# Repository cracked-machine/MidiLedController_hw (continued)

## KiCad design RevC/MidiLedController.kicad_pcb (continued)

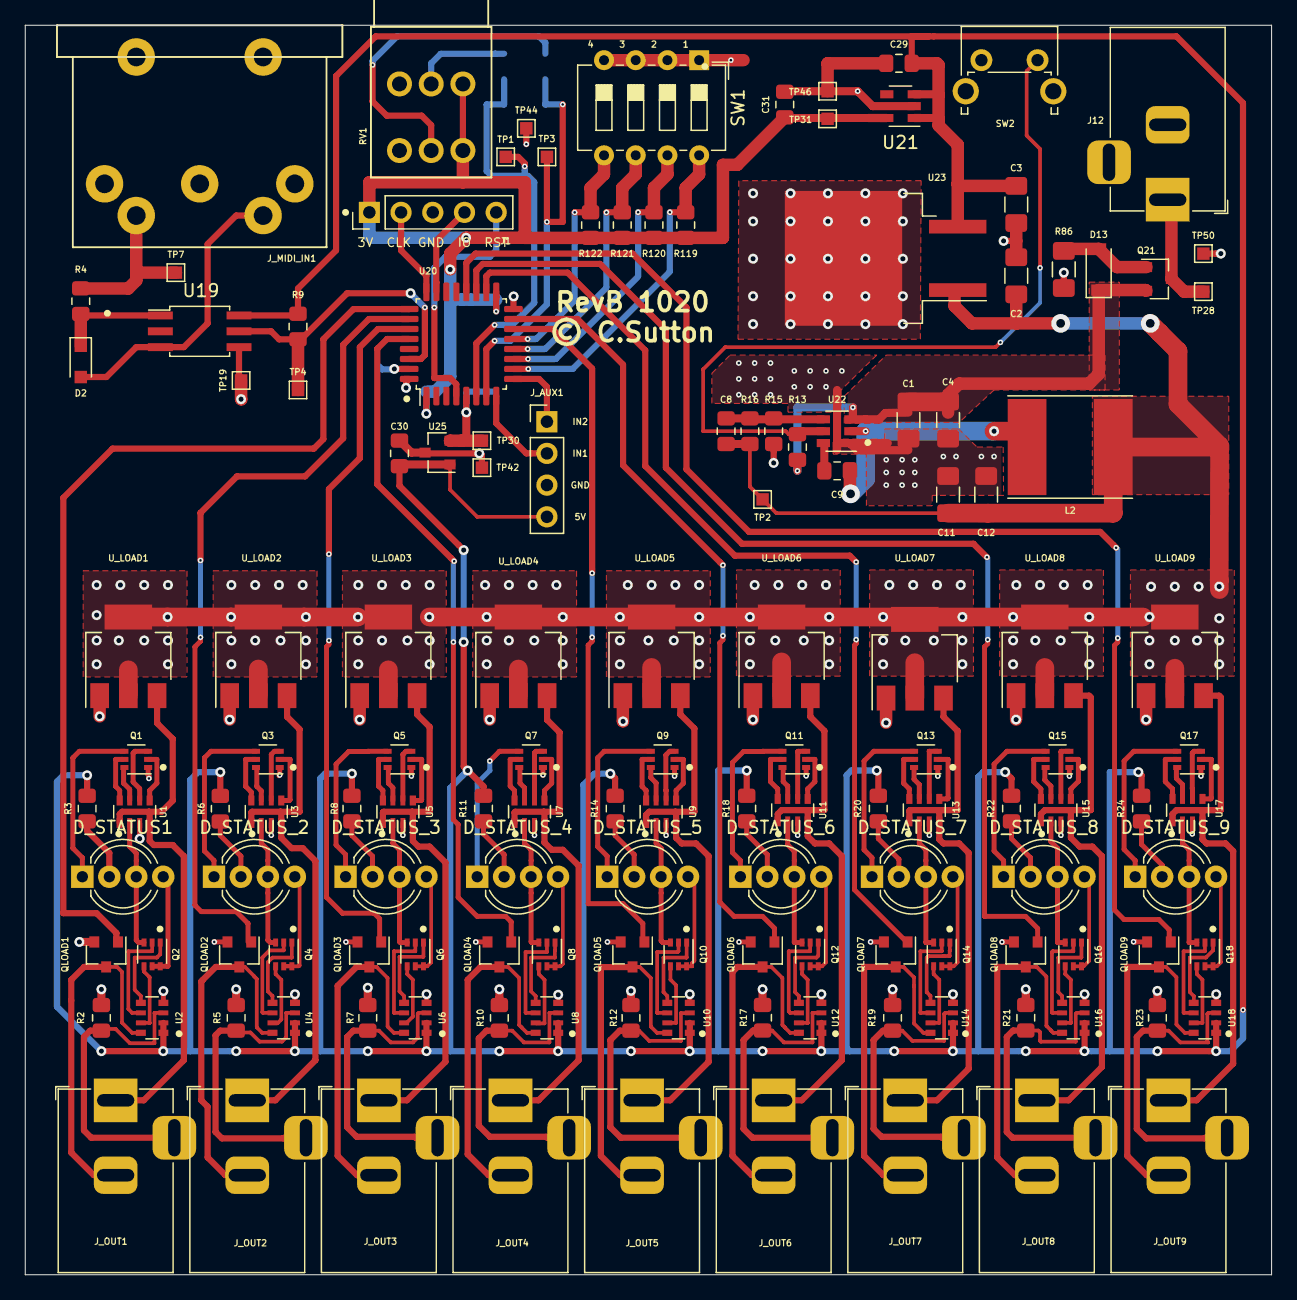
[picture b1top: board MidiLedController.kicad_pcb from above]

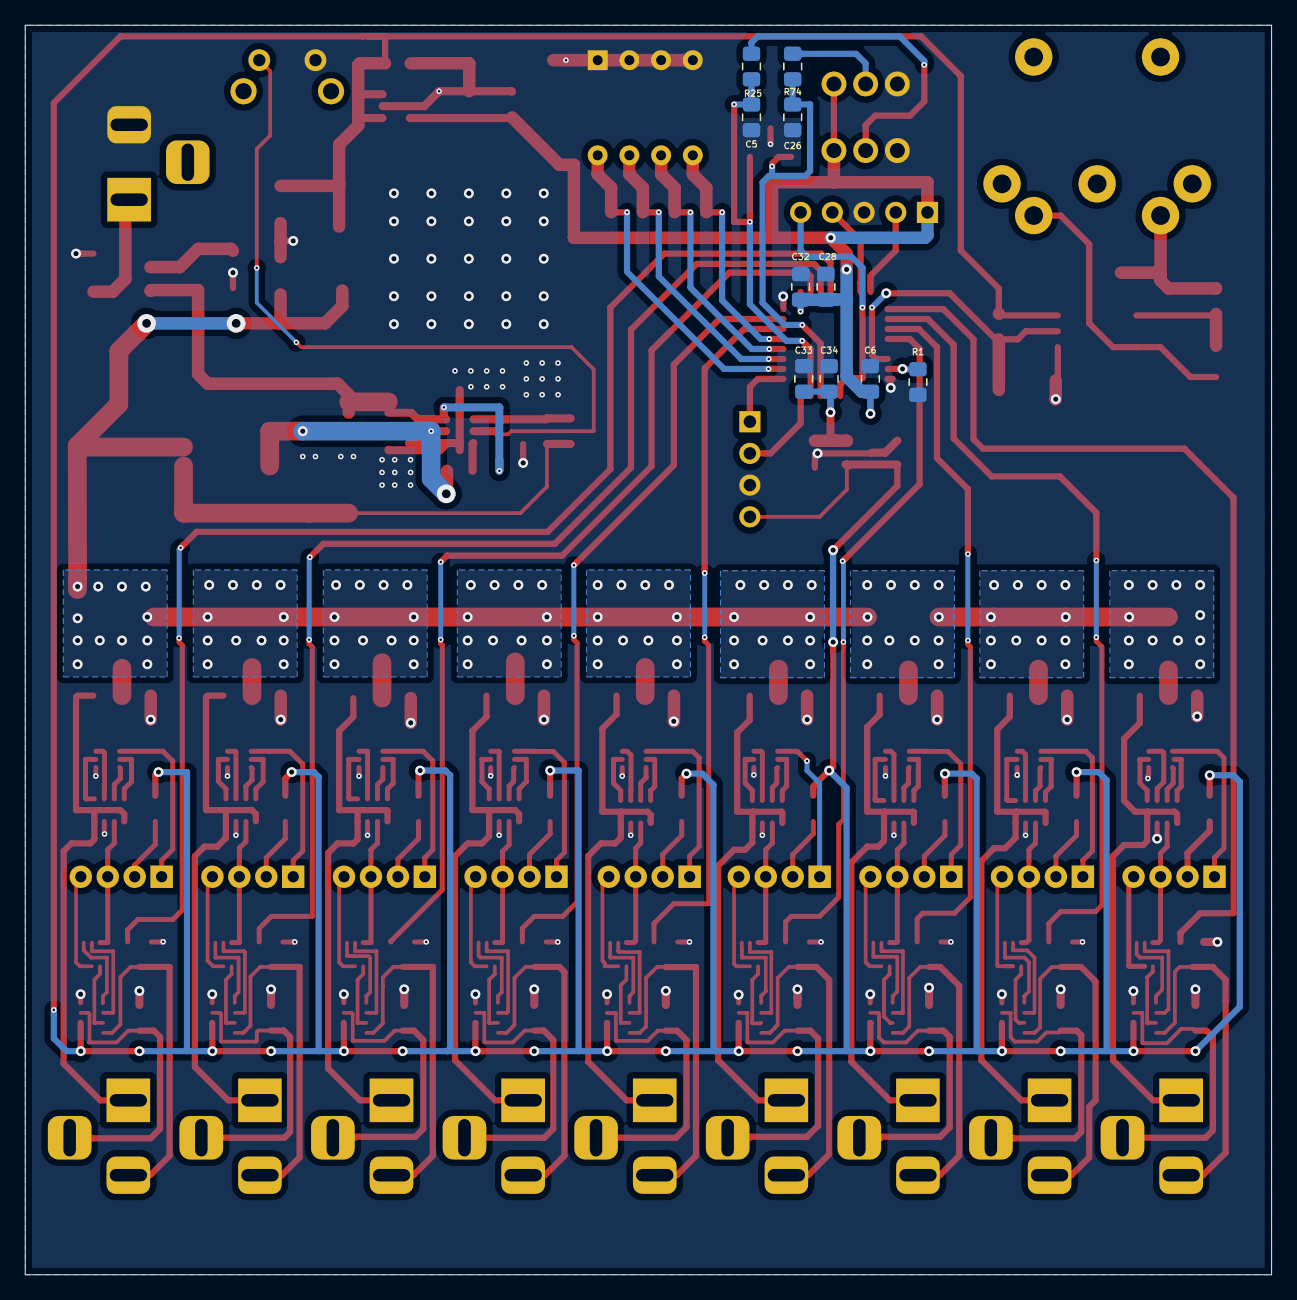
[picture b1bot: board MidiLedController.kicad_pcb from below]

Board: 2 copper layers, 99.8 x 100.1 mm, 151 parts (10 on the bottom side), 165 nets.

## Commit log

2019-12-28 RevA commit
2019-12-28 readme update
2019-12-30 HW
    - Added TODO list to Readme
    - Added PTH901 footprint (dual concentric pot) to lib folder
2019-12-30 HW: TPS SMPS
    - Increased VIN/GNDS trace width and included more ground vias for better thermal management
2020-01-16 updated HW
    changed single gang PTD901 to dual gang concentric PTH901
2020-01-18 Added some annotations to schematic
2020-03-02 create revB
2020-03-12 Created RevC
    Swapped LEDs for wider footprint
2020-03-22 Replaced 6N135 SMDIP8 with H11L1 SMDIP6
2020-03-22 Replaced H11L1 SMD6 with TLP2361 SO5
2020-03-23 hw update
    switched MCP1754 (SOT23-3) to LP3992 (SOT23-5)
2020-10-18 Added UserPots and RGB LEDS
    Updated schema docs
